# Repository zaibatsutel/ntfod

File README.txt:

HELLO INTERNET!

This is my version of the ever popular "connect your old computer to the
internet using wifi" project. 

This version uses (for now) the ESP-03, a slightly more broken out version
of the ESP-01. It has LEDs and stuff on it to show the state of control
registers and other things. 

The big thing that I wanted to implement here is that the flow control pins
are selectable!

There's some other things that I've done:

* I've used a MAX3386e (the SOIC20 version) so that I can make sure that I
have a good set of inputs and outputs. The big reason for this was so that
I can include a RING line (so you can dial into this!) and so that it had
all the various control lines that people integrated into their stuff.

Some day, I'd like to make this into a more product-like thing. 

The software is the apache2-licensed Zimodem from Bo Zimmerman. I'd like to
eventually have his software selectable in terms of what board it's being run
under so that there's fewer forks. His was designed with Commodore CBM machines
in mind -- mine is more built for the NEC Model 100s and friends. 

You can program this with the serial port that is included on the board if you
have a USB-Serial controller, but you still have to populate the buttons for
program and reset.

Programming involves holding down program and reset, then releasing reset.
This will place the device into boot mode (as is the case with all the various
things that use the ESP8266.)

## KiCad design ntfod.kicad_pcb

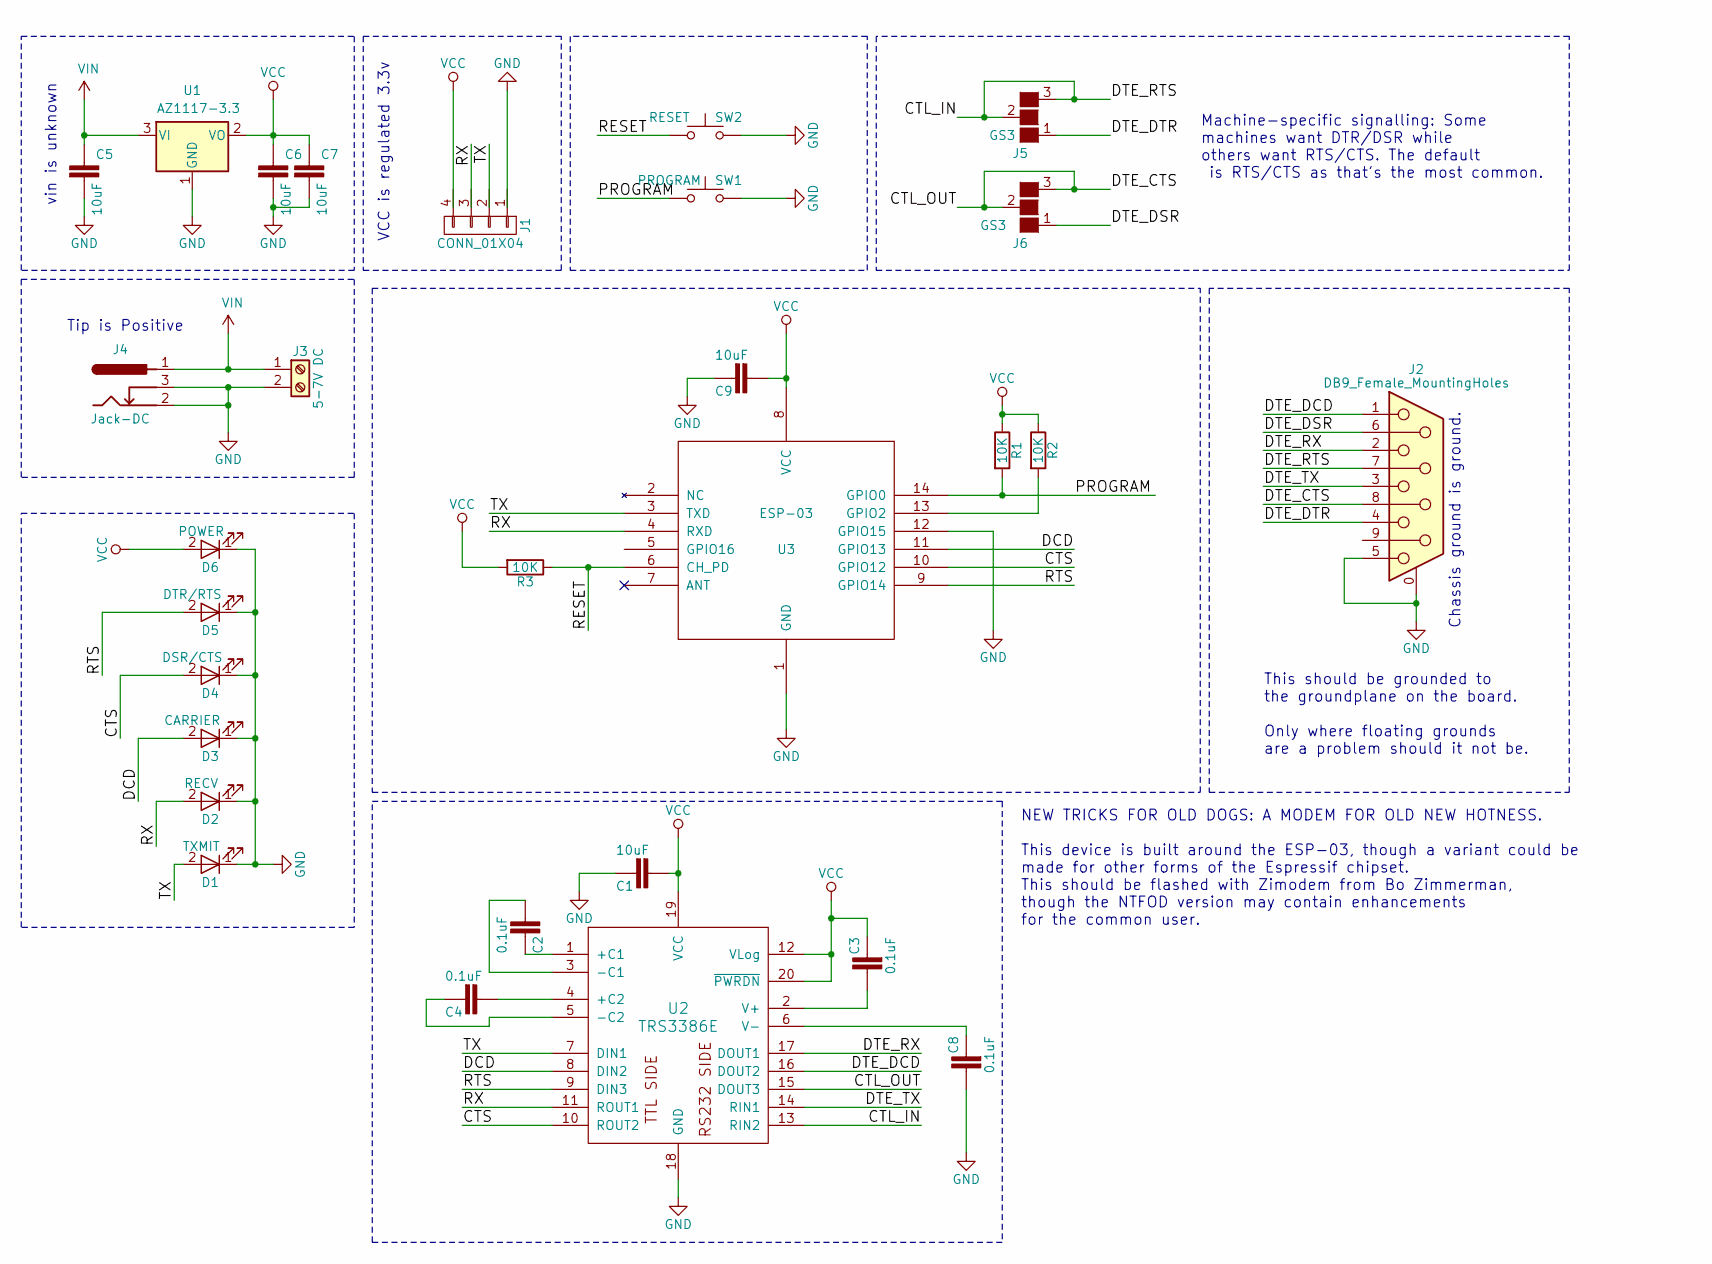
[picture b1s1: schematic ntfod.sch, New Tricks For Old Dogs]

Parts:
C1, C5, C6, C7, C9: 10uF; 1206
C2, C3, C4, C8: 0.1uF; 1206
D1: TXMIT; D_1206
D2: RECV; D_1206
D3: CARRIER; D_1206
D4: DSR/CTS; D_1206
D5: DTR/RTS; D_1206
D6: POWER; D_1206
J1: CONN_01X04; Pin_Header_Straight_1x04
J2: DB9_Female_MountingHoles; DB9
J3: 5-7V DC; PINHEAD1-2
J4: Jack-DC; BARREL_JACK
J5, J6: GS3
R1, R2, R3: 10K; R_1206_HandSoldering
SW1: PROGRAM; SW_SPST_TL3342
SW2: RESET; SW_SPST_TL3342
U1: AZ1117-3.3; SOT-223-3_TabPin2
U2: TRS3386E; SOIC-20W_7.5x12.8mm_Pitch1.27mm
U3: ESP-03

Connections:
/CTL_IN: J2.7, J5.2 (G2), J5.3 (G3), U2.13 (RIN2)
/CTL_OUT: J2.8, J6.2 (G2), J6.3 (G3), U2.15 (DOUT3)
/CTS: D4.2 (A), U2.10 (ROUT2), U3.10 (GPIO12)
/DCD: D3.2 (A), U2.8 (DIN2), U3.11 (GPIO13)
/DTE_DCD: J2.1, U2.16 (DOUT2)
/DTE_DSR: J2.6, J6.1 (G1)
/DTE_DTR: J2.4, J5.1 (G1)
/DTE_RX: J2.2, U2.17 (DOUT1)
/DTE_TX: J2.3, U2.14 (RIN1)
/PROGRAM: R1.2, SW1.1, U3.14 (GPIO0)
/RESET: R3.1, SW2.1, U3.6 (CH_PD)
/RTS: D5.2 (A), U2.9 (DIN3), U3.9 (GPIO14)
/RX: D2.2 (A), J1.3, U2.11 (ROUT1), U3.4 (RXD)
/TX: D1.2 (A), J1.2, U2.7 (DIN1), U3.3 (TXD)
GND: C1.2, C5.2, C6.2, C7.2, C8.1, C9.2, D1.1 (K), D2.1 (K), D3.1 (K), D4.1 (K), D5.1 (K), D6.1 (K), J1.1, J2.0 (PAD), J2.5, J3.2, J4.2, J4.3, SW1.2, SW2.2, U1.1 (GND), U2.18 (GND), U3.1 (GND), U3.12 (GPIO15)
unnamed: C2.1, U2.3 (-C1)
unnamed: C2.2, U2.1 (+C1)
unnamed: C3.1, U2.2 (V+)
unnamed: C4.1, U2.4 (+C2)
unnamed: C4.2, U2.5 (-C2)
unnamed: C8.2, U2.6 (V-)
unnamed: R2.2, U3.13 (GPIO2)
VCC: C1.1, C3.2, C6.1, C7.1, C9.1, D6.2 (A), J1.4, R1.1, R2.1, R3.2, U1.2 (VO), U2.12 (VLog), U2.19 (VCC), U2.20 (~PWRDN), U3.8 (VCC)
VIN: C5.1, J3.1, J4.1, U1.3 (VI)

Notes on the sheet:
vin is unknown
VCC is regulated 3.3v
Tip is Positive
Chassis ground is ground.
Machine-specific signalling: Some machines want DTR/DSR while others want RTS/CTS. The default is RTS/CTS as that's the most common.
This should be grounded to the groundplane on the board. Only where floating grounds are a problem should it not be.
NEW TRICKS FOR OLD DOGS: A MODEM FOR OLD NEW HOTNESS. This device is built around the ESP-03, though a variant could be made for other forms of the Espressif chipset. This should be flashed with Zimodem from Bo Zimmerman, though the NTFOD version may contain enhancements for the common user.

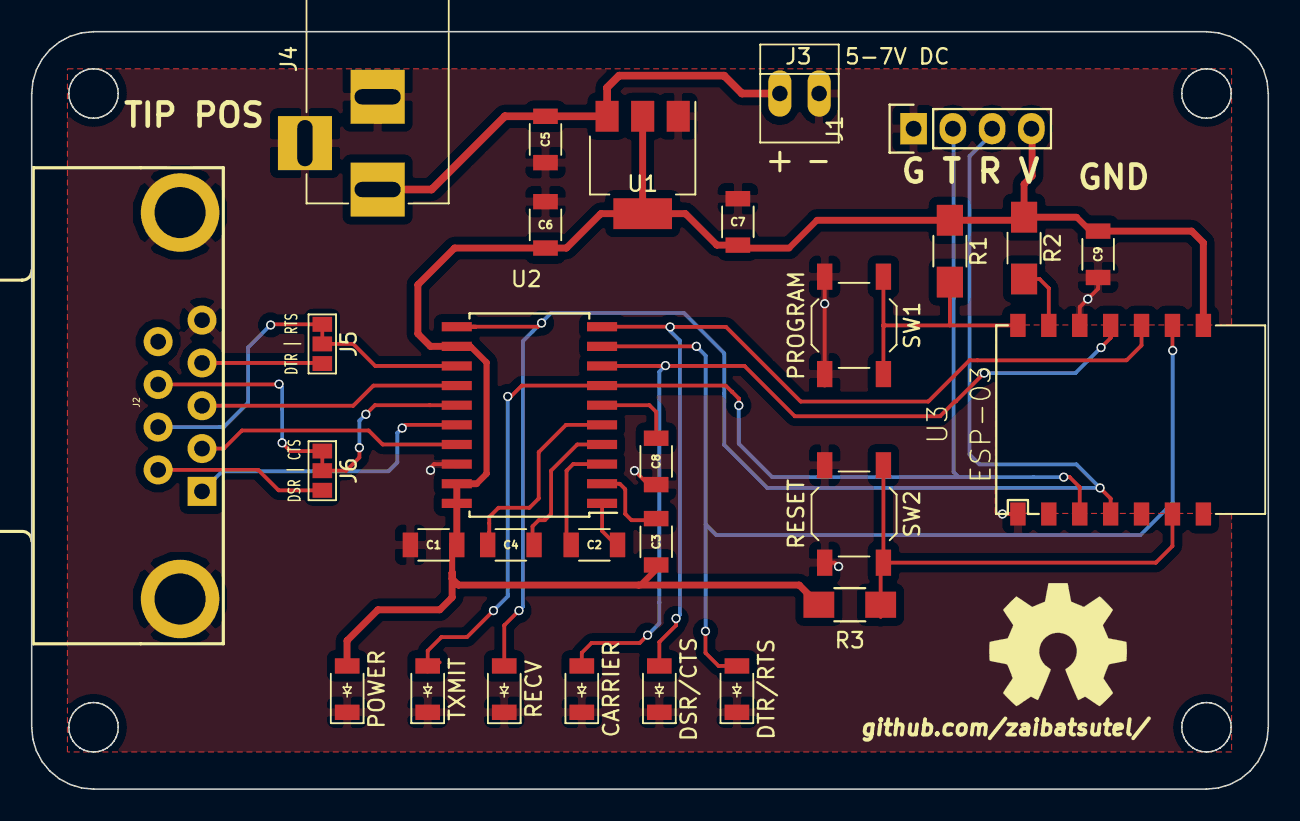
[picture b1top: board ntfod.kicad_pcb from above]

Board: 2 copper layers, 80.0 x 49.0 mm, 29 parts (0 on the bottom side), 24 nets.

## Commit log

2018-09-08 initial commit.
2018-09-08 Initial board shots
2018-09-09 Initial gerber and schematic pdfs
    This is revision 2: The first revision I care to release to the world.
    I'll tell you how it goes when I have actual, physical boards in my
    actual physical hands.
2018-09-11 initial BOM, PCB finish.
2018-09-13 update gitignore

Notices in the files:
ntfod.sch:
This document licensed CC-BY-SA
